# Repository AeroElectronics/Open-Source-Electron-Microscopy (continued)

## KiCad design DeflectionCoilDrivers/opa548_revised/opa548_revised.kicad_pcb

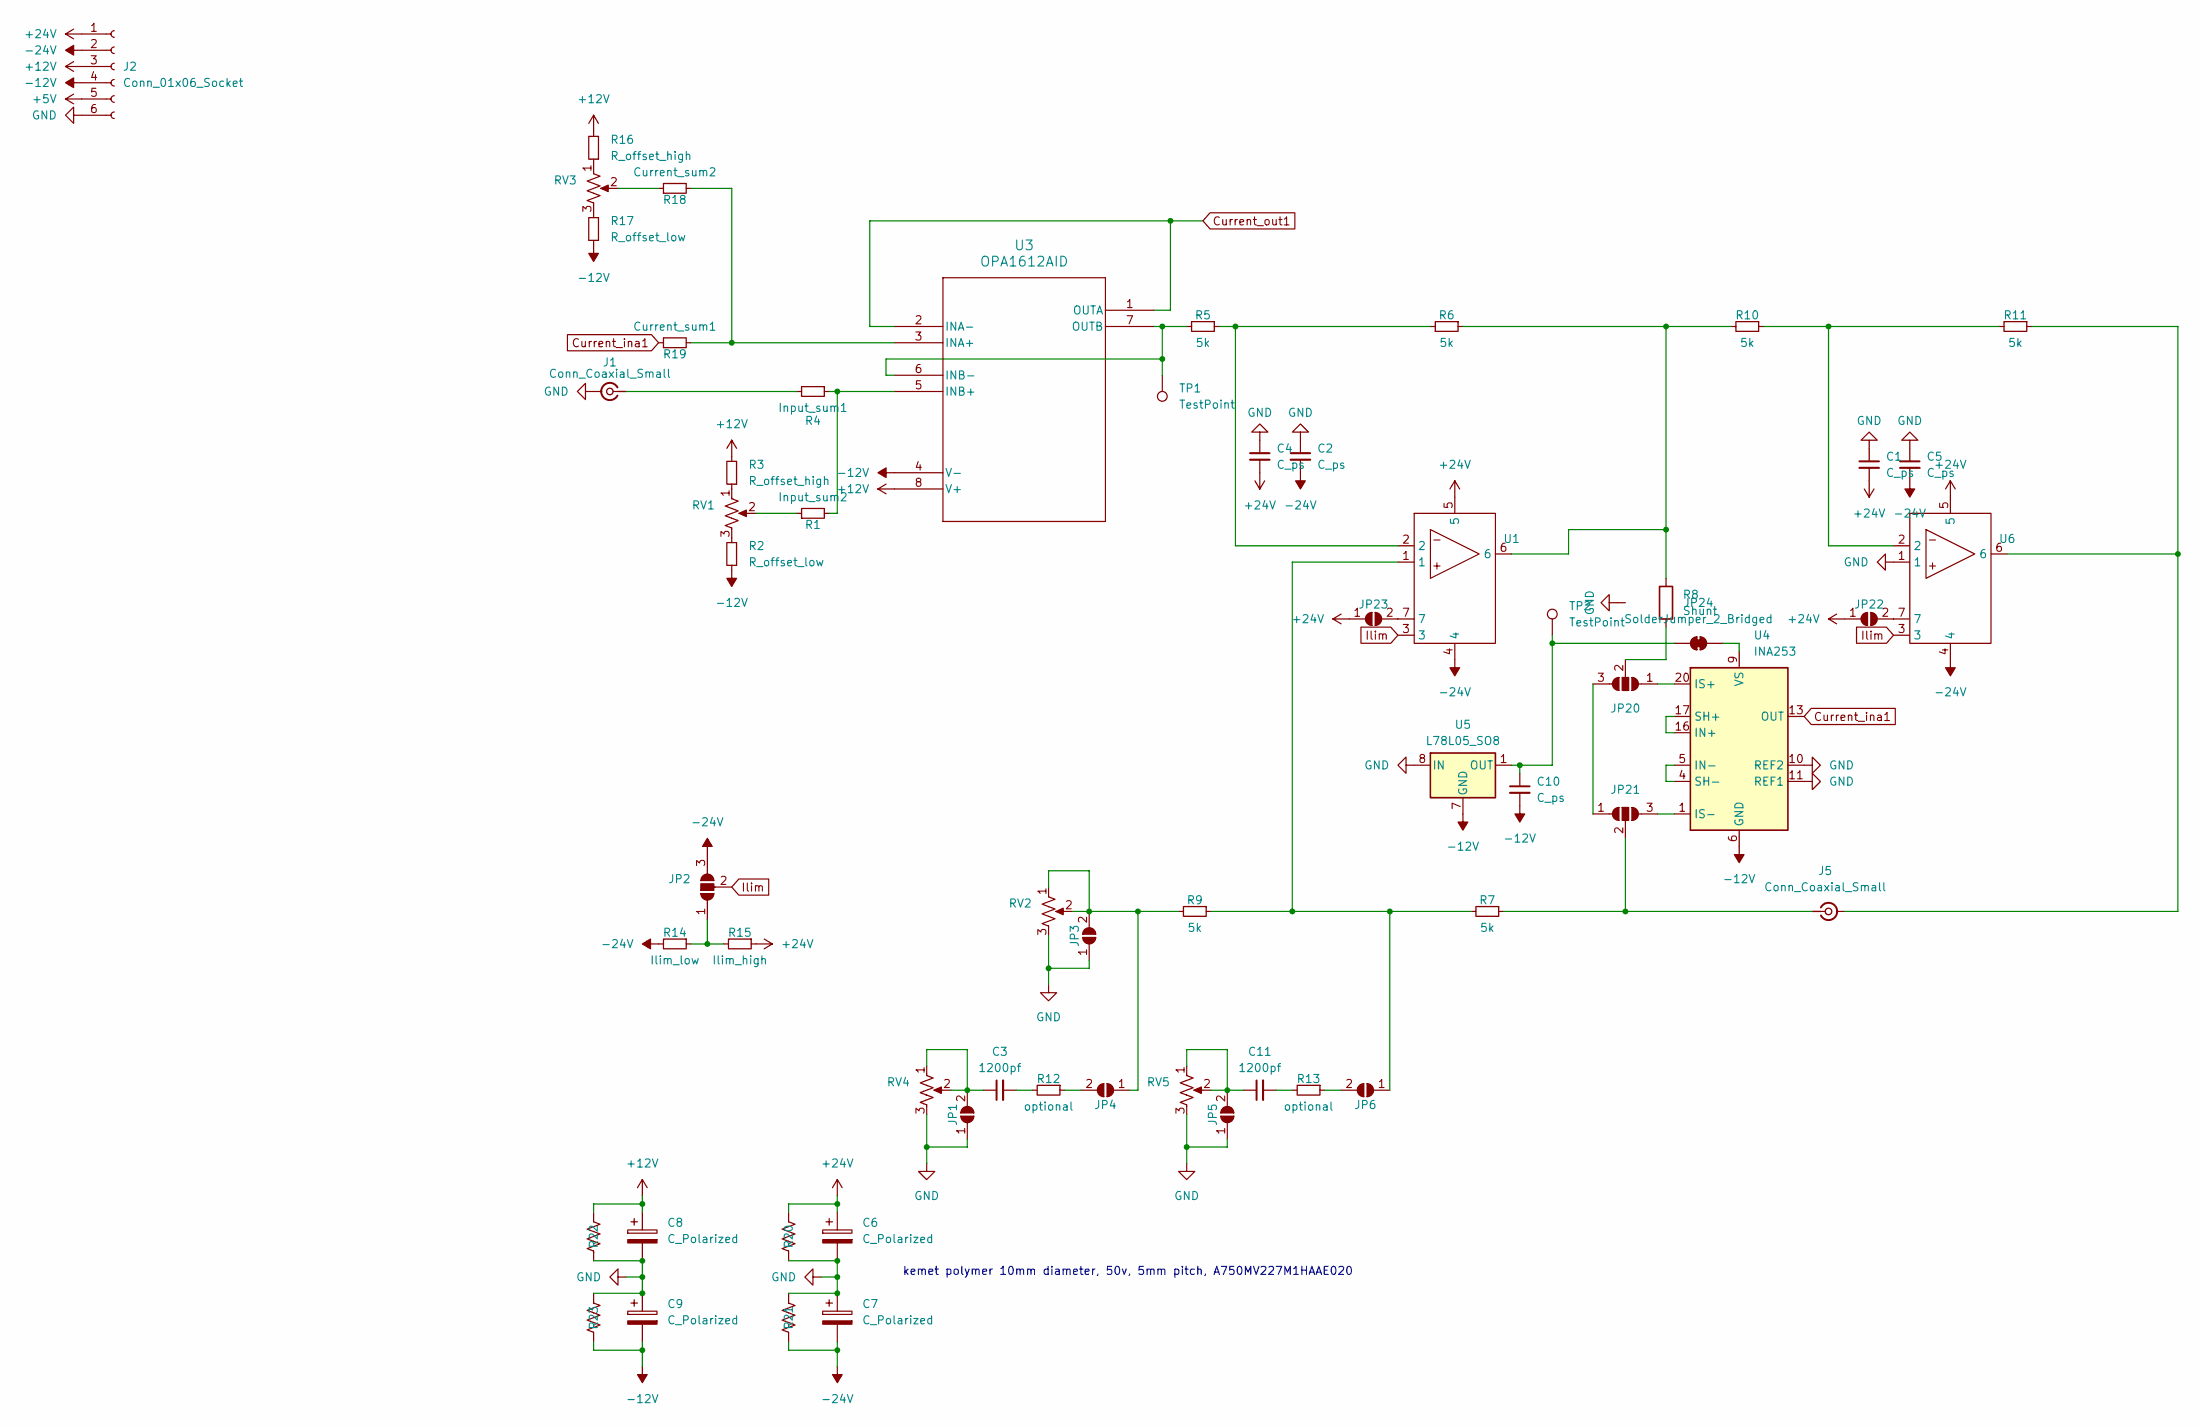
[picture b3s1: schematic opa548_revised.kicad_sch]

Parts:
C1, C2, C4, C5, C10: C_ps; C_0603_1608Metric_Pad1.08x0.95mm_HandSolder
C3, C11: 1200pf; C_0603_1608Metric_Pad1.08x0.95mm_HandSolder
C6, C7, C8, C9: C_Polarized; CP_Radial_D10.0mm_P5.00mm
J1, J5: Conn_Coaxial_Small; BNC_Amphenol_B6252HB-NPP3G-50_Horizontal
J2: Conn_01x06_Socket; PhoenixContact_MC_1,5_6-GF-3.81_1x06_P3.81mm_Horizontal_Thr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
JP1, JP3, JP4, JP5, JP6, JP22, JP23: SolderJumper_2_Open; SolderJumper-2_P1.3mm_Open_RoundedPad1.0x1.5mm
JP2, JP20, JP21: SolderJumper_3_Open; SolderJumper-3_P1.3mm_Open_RoundedPad1.0x1.5mm
JP24: SolderJumper_2_Bridged; SolderJumper-2_P1.3mm_Bridged_RoundedPad1.0x1.5mm
R1: Input_sum2; R_0603_1608Metric_Pad0.98x0.95mm_HandSolder
R2, R17: R_offset_low; R_0603_1608Metric_Pad0.98x0.95mm_HandSolder
R3, R16: R_offset_high; R_0603_1608Metric_Pad0.98x0.95mm_HandSolder
R4: Input_sum1; R_0603_1608Metric_Pad0.98x0.95mm_HandSolder
R5, R6, R7, R9, R10, R11: 5k; R_0603_1608Metric_Pad0.98x0.95mm_HandSolder
R8: Shunt; TO-263-2_TabPin1
R12, R13: optional; R_0603_1608Metric_Pad0.98x0.95mm_HandSolder
R14: Ilim_low; R_0603_1608Metric_Pad0.98x0.95mm_HandSolder
R15: Ilim_high; R_0603_1608Metric_Pad0.98x0.95mm_HandSolder
R18: Current_sum2; R_0603_1608Metric_Pad0.98x0.95mm_HandSolder
R19: Current_sum1; R_0603_1608Metric_Pad0.98x0.95mm_HandSolder
R20, R21, R22, R23: 100k; R_0603_1608Metric_Pad0.98x0.95mm_HandSolder
RV1, RV2, RV3, RV4, RV5: R_Potentiometer_US; Potentiometer_Bourns_3269P_Horizontal
TP1, TP2: TestPoint; PinSocket_1x01_P2.54mm_Vertical
U1, U6: opa548
U3: OPA1612AID; opa1612
U4: INA253; TSSOP-20_4.4x6.5mm_P0.65mm
U5: L78L05_SO8; SOIC-8_3.9x4.9mm_P1.27mm

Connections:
+5V: J2.5
+12V: C8.1, J2.3, R3.2, R16.2, R22.2, U3.8 (V+)
+24V: C1.2, C4.2, C6.1, J2.1, JP22.1 (A), JP23.1 (A), R15.1, R20.2, U1.5, U6.5
-12V: C9.2, C10.2, J2.4, R2.1, R17.1, R23.1, U3.4 (V-), U4.6 (GND), U4.15 (GND), U5.2 (GND), U5.3 (GND), U5.6 (GND), U5.7 (GND)
-24V: C2.2, C5.2, C7.2, J2.2, JP2.3 (B), R14.2, R21.1, U1.4, U6.4
Current_ina1: R19.1, U4.13 (OUT)
Current_out1: U3.1 (OUTA), U3.2 (INA-)
GND: C1.1, C2.1, C4.1, C5.1, C6.2, C7.1, C8.2, C9.1, J1.2 (Ext), J2.6, JP1.1 (A), JP3.1 (A), JP5.1 (A), R8.3, R20.1, R21.2, R22.1, R23.2, RV2.3, RV4.3, RV5.3, U4.10 (REF2), U4.11 (REF1), U5.8 (IN), U6.1
Ilim: JP2.2 (C), U1.3, U6.3
unnamed: C3.2, R12.2
unnamed: C11.2, R13.2
unnamed: J1.1 (In), R4.2
unnamed: J5.2 (Ext), R11.1, U6.6
unnamed: J5.1 (In), JP21.2 (C), R7.1
unnamed: C3.1, JP1.2 (B), RV4.1, RV4.2
unnamed: JP2.1 (A), R14.1, R15.2
unnamed: JP3.2 (B), JP4.1 (A), R9.2, RV2.1, RV2.2
unnamed: JP4.2 (B), R12.1
unnamed: C11.1, JP5.2 (B), RV5.1, RV5.2
unnamed: JP6.1 (A), R7.2, R9.1, U1.1
unnamed: JP6.2 (B), R13.1
unnamed: JP20.1 (A), U4.18 (IS+), U4.19 (IS+), U4.20 (IS+)
unnamed: JP20.3 (B), JP21.1 (A)
unnamed: JP20.2 (C), R8.2
unnamed: JP21.3 (B), U4.1 (IS-), U4.2 (IS-), U4.3 (IS-)
unnamed: JP22.2 (B), U6.7
unnamed: JP23.2 (B), U1.7
unnamed: C10.1, JP24.1 (A), TP2.1, U5.1 (OUT)
unnamed: JP24.2 (B), U4.9 (VS)
unnamed: R1.1, RV1.2
unnamed: R2.2, RV1.3
unnamed: R3.1, RV1.1
unnamed: R5.1, R6.2, U1.2
unnamed: R10.1, R11.2, U6.2
unnamed: R6.1, R8.1, R10.2, U1.6
unnamed: R16.1, RV3.1
unnamed: R17.2, RV3.3
unnamed: R18.1, RV3.2
unnamed: R18.2, R19.2, U3.3 (INA+)
unnamed: R1.2, R4.1, U3.5 (INB+)
unnamed: R5.2, TP1.1, U3.6 (INB-), U3.7 (OUTB)
unnamed: U4.16 (IN+), U4.17 (SH+)
unnamed: U4.4 (SH-), U4.5 (IN-)

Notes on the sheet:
kemet polymer 10mm diameter, 50v, 5mm pitch, A750MV227M1HAAE020

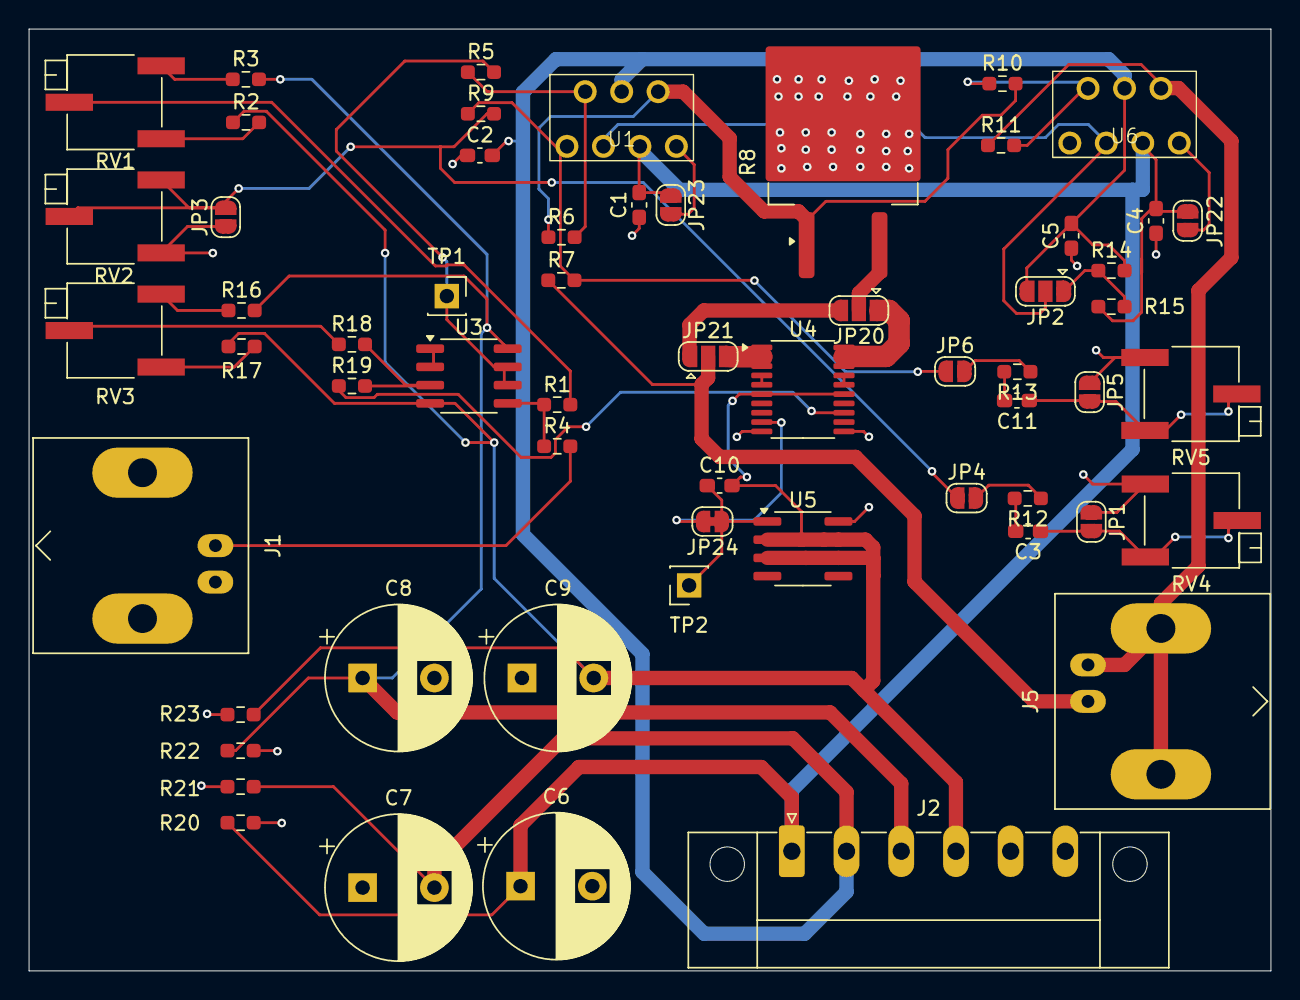
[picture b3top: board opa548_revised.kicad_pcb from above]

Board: 2 copper layers, 86.5 x 65.6 mm, 60 parts (0 on the bottom side), 42 nets.

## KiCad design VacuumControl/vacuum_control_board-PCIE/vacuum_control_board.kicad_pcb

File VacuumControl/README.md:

To open and close valves, read out voltages, or do whatver other control related tasks.

These boards are both STM32 microcontrollers with opto isolated output and analog IO hooked up to some headphone jacks. There are two versions, one with the microcontroller on a daugter board and one with the microcontroller layed out on the boards.

I havent tested this board yet, so you may want to hold off until I do. Also, I'm strongly considering switching to a raspberry pi or something else.

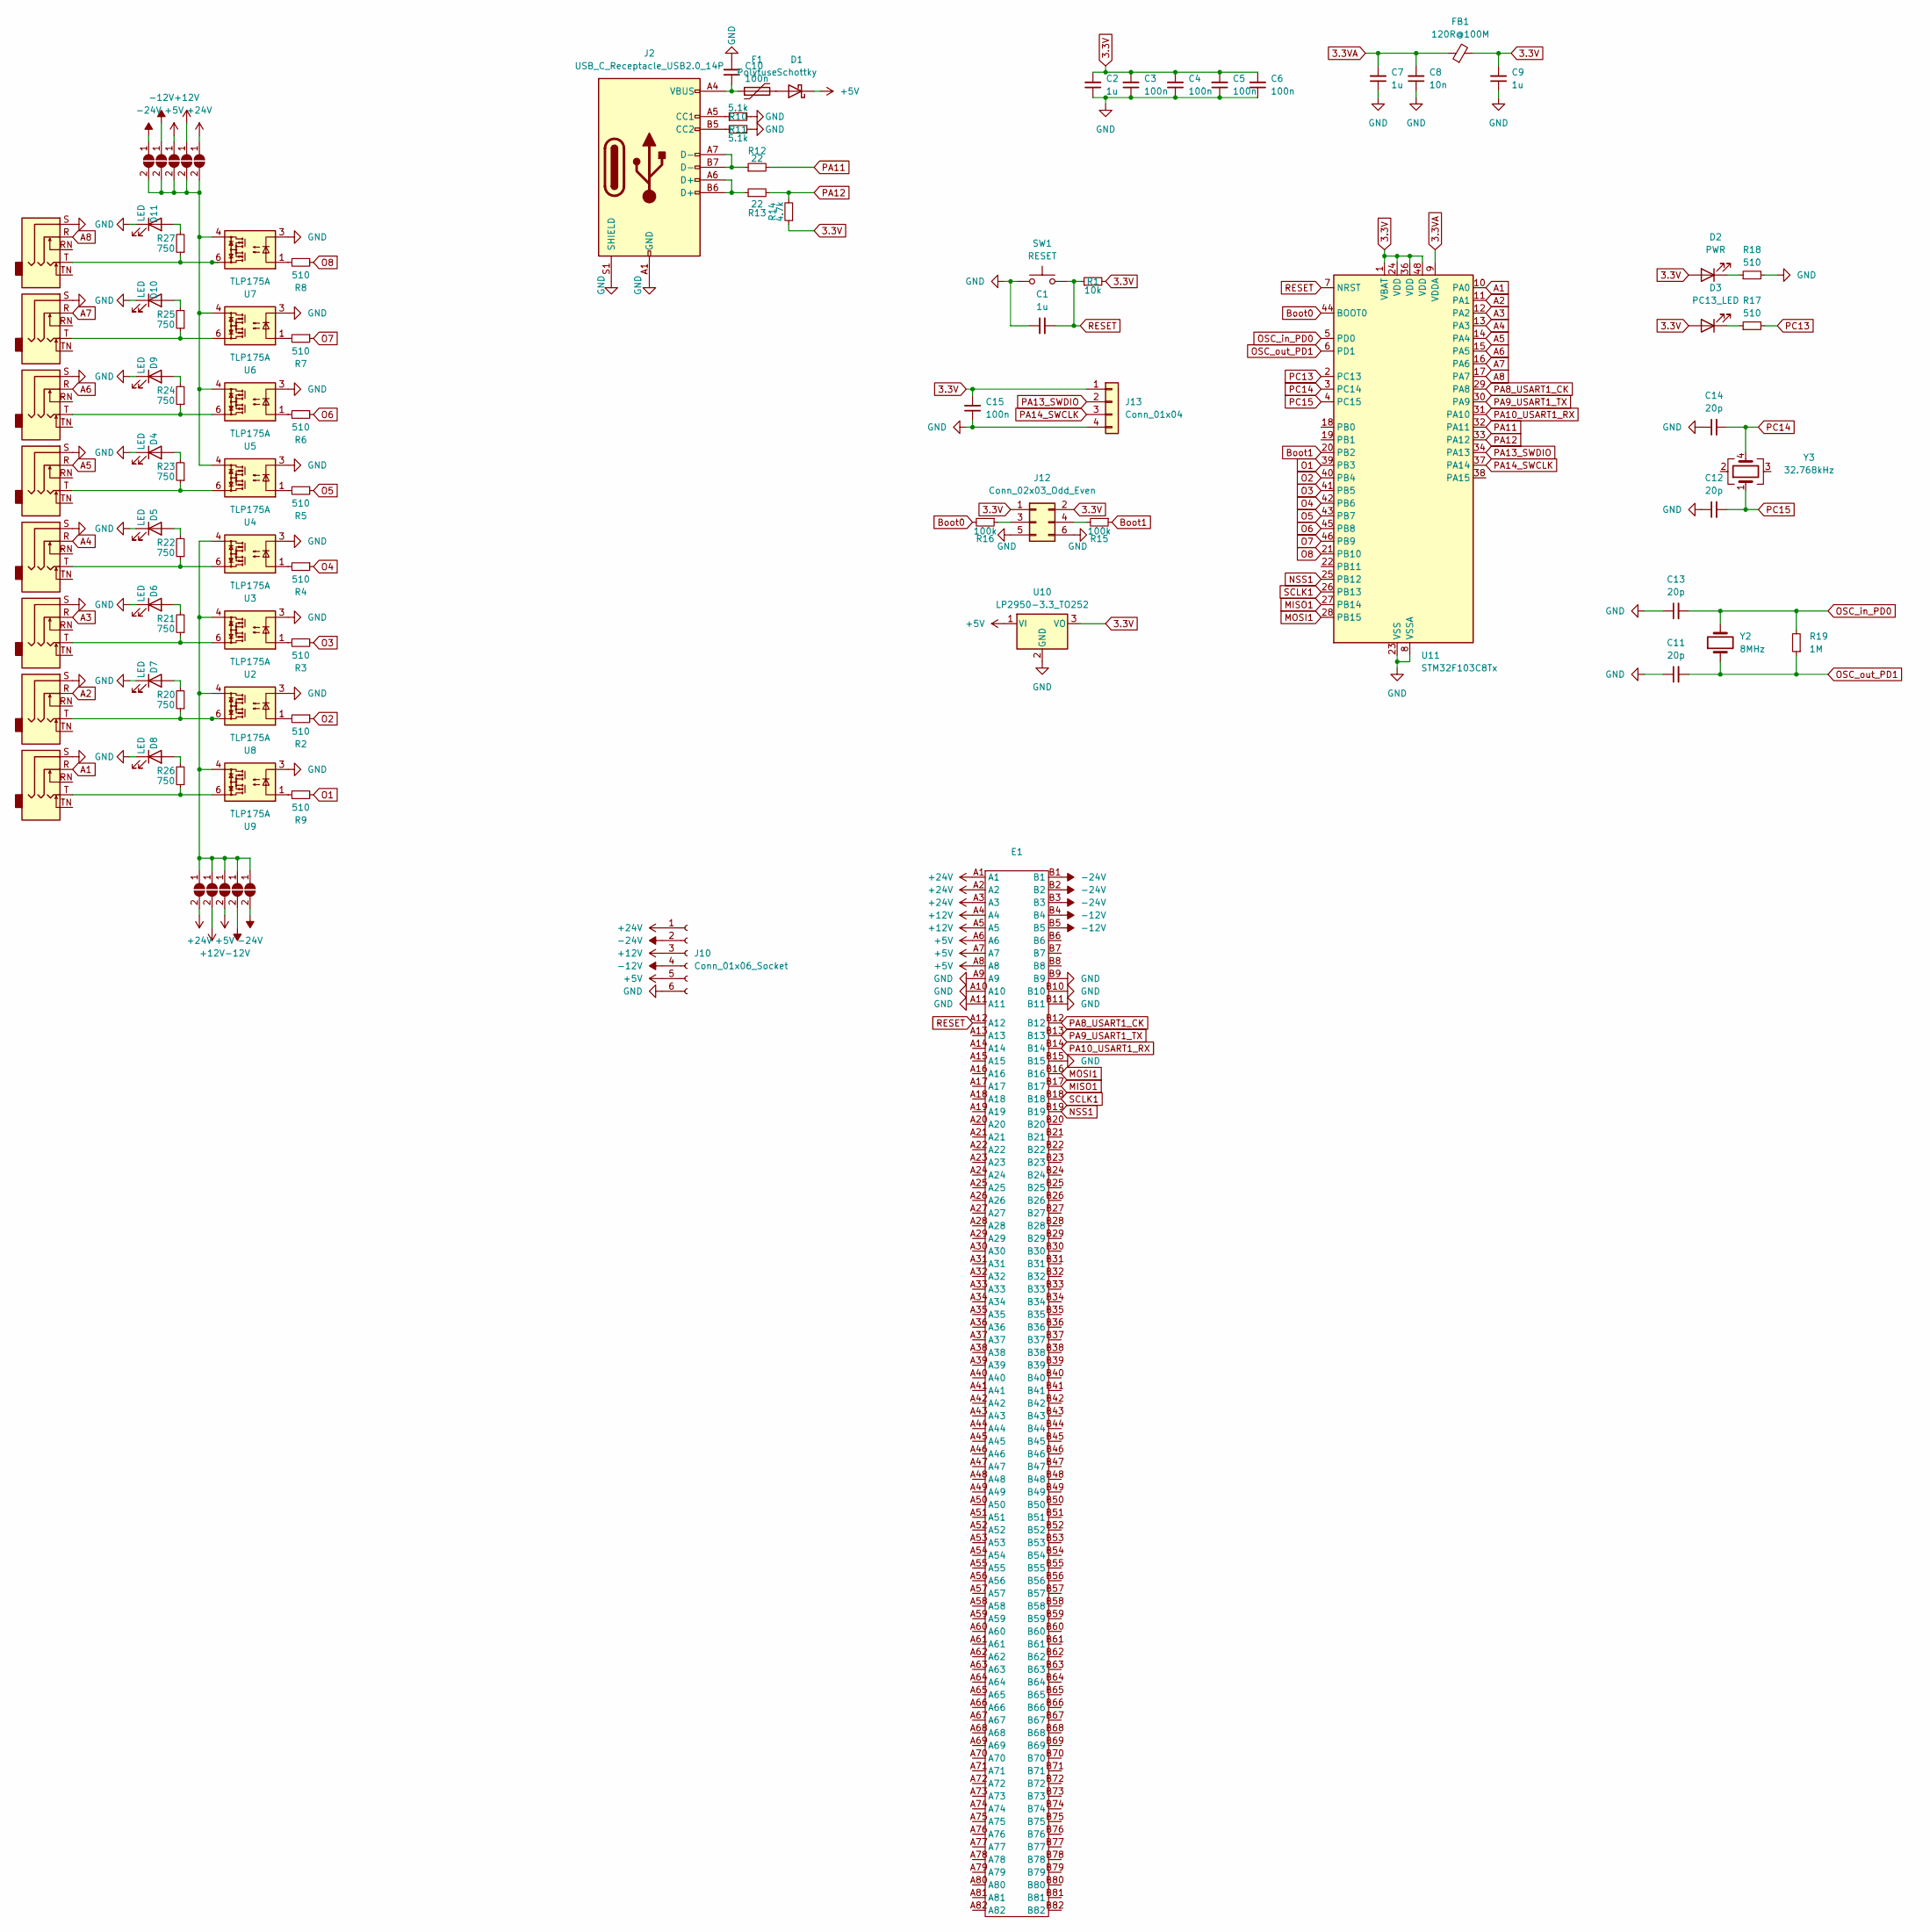
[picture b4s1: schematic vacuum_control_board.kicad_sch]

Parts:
C1, C2, C7, C9: 1u; C_0603_1608Metric_Pad1.08x0.95mm_HandSolder
C3, C4, C5, C6, C10, C15: 100n; C_0603_1608Metric_Pad1.08x0.95mm_HandSolder
C8: 10n; C_0603_1608Metric_Pad1.08x0.95mm_HandSolder
C11, C12, C13, C14: 20p; C_0603_1608Metric_Pad1.08x0.95mm_HandSolder
D1: Schottky; R_1210_3225Metric_Pad1.30x2.65mm_HandSolder
D2: PWR; LED_0603_1608Metric
D3: PC13_LED; LED_0603_1608Metric
D4, D5, D6, D7, D8, D9, D10, D11: LED; LED_0603_1608Metric_Pad1.05x0.95mm_HandSolder
E1: BUS_PCIexpress_x16
F1: Polyfuse; R_0603_1608Metric_Pad0.98x0.95mm_HandSolder
FB1: 120R@100M; C_0603_1608Metric_Pad1.08x0.95mm_HandSolder
J1, J3, J4, J5, J6, J7, J8, J9: AudioJack3_SwitchTR; Jack_3.5mm_CUI_SJ1-3535NG_Horizontal_CircularHoles
J2: USB_C_Receptacle_USB2.0_14P; USB_C_Receptacle_GCT_USB4105-xx-A_16P_TopMnt_Horizontal
J10: Conn_01x06_Socket; PhoenixContact_MC_1,5_6-GF-3.81_1x06_P3.81mm_Horizontal_Thr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
J12: Conn_02x03_Odd_Even; PinHeader_2x03_P2.54mm_Vertical
J13: Conn_01x04; PinSocket_1x04_P2.54mm_Vertical
JP1, JP2, JP3, JP4, JP5, JP6, JP7, JP8, JP9, JP10: SolderJumper_2_Open; SolderJumper-2_P1.3mm_Open_RoundedPad1.0x1.5mm
R1: 10k; R_0603_1608Metric_Pad0.98x0.95mm_HandSolder
R2, R3, R4, R5, R6, R7, R8, R9, R17, R18: 510; R_0603_1608Metric_Pad0.98x0.95mm_HandSolder
R10, R11: 5.1k; R_0603_1608Metric_Pad0.98x0.95mm_HandSolder
R12, R13: 22; R_0603_1608Metric_Pad0.98x0.95mm_HandSolder
R14: 4.7k; R_0603_1608Metric_Pad0.98x0.95mm_HandSolder
R15, R16: 100k; R_0603_1608Metric_Pad0.98x0.95mm_HandSolder
R19: 1M; R_0603_1608Metric_Pad0.98x0.95mm_HandSolder
R20, R21, R22, R23, R24, R25, R26, R27: 750; R_0603_1608Metric_Pad0.98x0.95mm_HandSolder
SW1: RESET; SW_Push_1P1T_NO_Vertical_Wuerth_434133025816
U2, U3, U4, U5, U6, U7, U8, U9: TLP175A; MFSOP6-4_4.4x3.6mm_P1.27mm
U10: LP2950-3.3_TO252; TO-252-2
U11: STM32F103C8Tx; LQFP-48_7x7mm_P0.5mm
Y2: 8MHz; Crystal_HC49-4H_Vertical
Y3: 32.768kHz; Crystal_SMD_SeikoEpson_MC306-4Pin_8.0x3.2mm_HandSoldering

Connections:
3.3V: C2.2, C3.2, C4.2, C5.2, C6.2, C9.2, C15.2, D2.2 (A), D3.2 (A), FB1.2, J12.1, J12.2, J13.1, R1.2, R14.1, U10.3 (VO), U11.1 (VBAT), U11.24 (VDD), U11.36 (VDD), U11.48 (VDD)
3.3VA: C7.2, C8.2, FB1.1, U11.9 (VDDA)
+5V: D1.1 (K), E1.A6, E1.A7, E1.A8, J10.5, JP2.1 (A), JP8.2 (B), U10.1 (VI)
+12V: E1.A4, E1.A5, J10.3, JP3.1 (A), JP9.2 (B)
+24V: E1.A1, E1.A2, E1.A3, J10.1, JP4.1 (A), JP10.2 (B)
-12V: E1.B4, E1.B5, J10.4, JP1.1 (A), JP7.2 (B)
-24V: E1.B1, E1.B2, E1.B3, J10.2, JP5.1 (A), JP6.2 (B)
A1: J3.R, U11.10 (PA0)
A2: J1.R, U11.11 (PA1)
A3: J4.R, U11.12 (PA2)
A4: J5.R, U11.13 (PA3)
A5: J6.R, U11.14 (PA4)
A6: J7.R, U11.15 (PA5)
A7: J8.R, U11.16 (PA6)
A8: J9.R, U11.17 (PA7)
Boot0: R16.2, U11.44 (BOOT0)
Boot1: R15.1, U11.20 (PB2)
GND: C1.1, C2.1, C3.1, C4.1, C5.1, C6.1, C7.1, C8.1, C9.1, C10.2, C11.1, C12.1, C13.1, C14.1, C15.1, D4.1 (K), D5.1 (K), D6.1 (K), D7.1 (K), D8.1 (K), D9.1 (K), D10.1 (K), D11.1 (K), E1.A9, E1.A10, E1.A11, E1.B9, E1.B10, E1.B11, E1.B15, J1.S, J2.A1 (GND), J2.A12 (GND), J2.B1 (GND), J2.B12 (GND), J2.S1 (SHIELD), J3.S, J4.S, J5.S, J6.S, J7.S, J8.S, J9.S, J10.6, J12.5, J12.6, J13.4, R10.2, R11.2, R18.2, SW1.1, U2.3, U3.3, U4.3, U5.3, U6.3, U7.3, U8.3, U9.3, U10.2 (GND), U11.8 (VSSA), U11.23 (VSS), U11.35 (VSS), U11.47 (VSS)
MISO1: E1.B17, U11.27 (PB14)
MOSI1: E1.B16, U11.28 (PB15)
NSS1: E1.B19, U11.25 (PB12)
unnamed: C10.1, F1.1, J2.A4 (VBUS), J2.A9 (VBUS), J2.B4 (VBUS), J2.B9 (VBUS)
unnamed: D1.2 (A), F1.2
unnamed: D2.1 (K), R18.1
unnamed: D3.1 (K), R17.1
unnamed: D4.2 (A), R23.2
unnamed: D5.2 (A), R22.2
unnamed: D6.2 (A), R21.2
unnamed: D7.2 (A), R20.2
unnamed: D8.2 (A), R26.2
unnamed: D9.2 (A), R24.2
unnamed: D10.2 (A), R25.2
unnamed: D11.2 (A), R27.2
unnamed: J1.T, R20.1, U8.6
unnamed: J2.A5 (CC1), R10.1
unnamed: J2.B5 (CC2), R11.1
unnamed: J2.A6 (D+), J2.B6 (D+), R13.1
unnamed: J2.A7 (D-), J2.B7 (D-), R12.1
unnamed: J3.T, R26.1, U9.6
unnamed: J4.T, R21.1, U2.6
unnamed: J5.T, R22.1, U3.6
unnamed: J6.T, R23.1, U4.6
unnamed: J7.T, R24.1, U5.6
unnamed: J8.T, R25.1, U6.6
unnamed: J9.T, R27.1, U7.6
unnamed: J12.3, R16.1
unnamed: J12.4, R15.2
unnamed: JP1.2 (B), JP2.2 (B), JP3.2 (B), JP4.2 (B), JP5.2 (B), U4.4, U5.4, U6.4, U7.4
unnamed: JP6.1 (A), JP7.1 (A), JP8.1 (A), JP9.1 (A), JP10.1 (A), U2.4, U3.4, U8.4, U9.4
unnamed: R2.2, U8.1
unnamed: R3.2, U2.1
unnamed: R4.2, U3.1
unnamed: R5.2, U4.1
unnamed: R6.2, U5.1
unnamed: R7.2, U6.1
unnamed: R8.2, U7.1
unnamed: R9.2, U9.1
O1: R9.1, U11.39 (PB3)
O2: R2.1, U11.40 (PB4)
O3: R3.1, U11.41 (PB5)
O4: R4.1, U11.42 (PB6)
O5: R5.1, U11.43 (PB7)
O6: R6.1, U11.45 (PB8)
O7: R7.1, U11.46 (PB9)
O8: R8.1, U11.21 (PB10)
OSC_in_PD0: C13.2, R19.2, U11.5 (PD0), Y2.2
OSC_out_PD1: C11.2, R19.1, U11.6 (PD1), Y2.1
PA8_USART1_CK: E1.B12, U11.29 (PA8)
PA9_USART1_TX: E1.B13, U11.30 (PA9)
PA10_USART1_RX: E1.B14, U11.31 (PA10)
PA11: R12.2, U11.32 (PA11)
PA12: R13.2, R14.2, U11.33 (PA12)
PA13_SWDIO: J13.2, U11.34 (PA13)
PA14_SWCLK: J13.3, U11.37 (PA14)
PC13: R17.2, U11.2 (PC13)
PC14: C14.2, U11.3 (PC14), Y3.4
PC15: C12.2, U11.4 (PC15), Y3.1
RESET: C1.2, E1.A12, R1.1, SW1.2, U11.7 (NRST)
SCLK1: E1.B18, U11.26 (PB13)

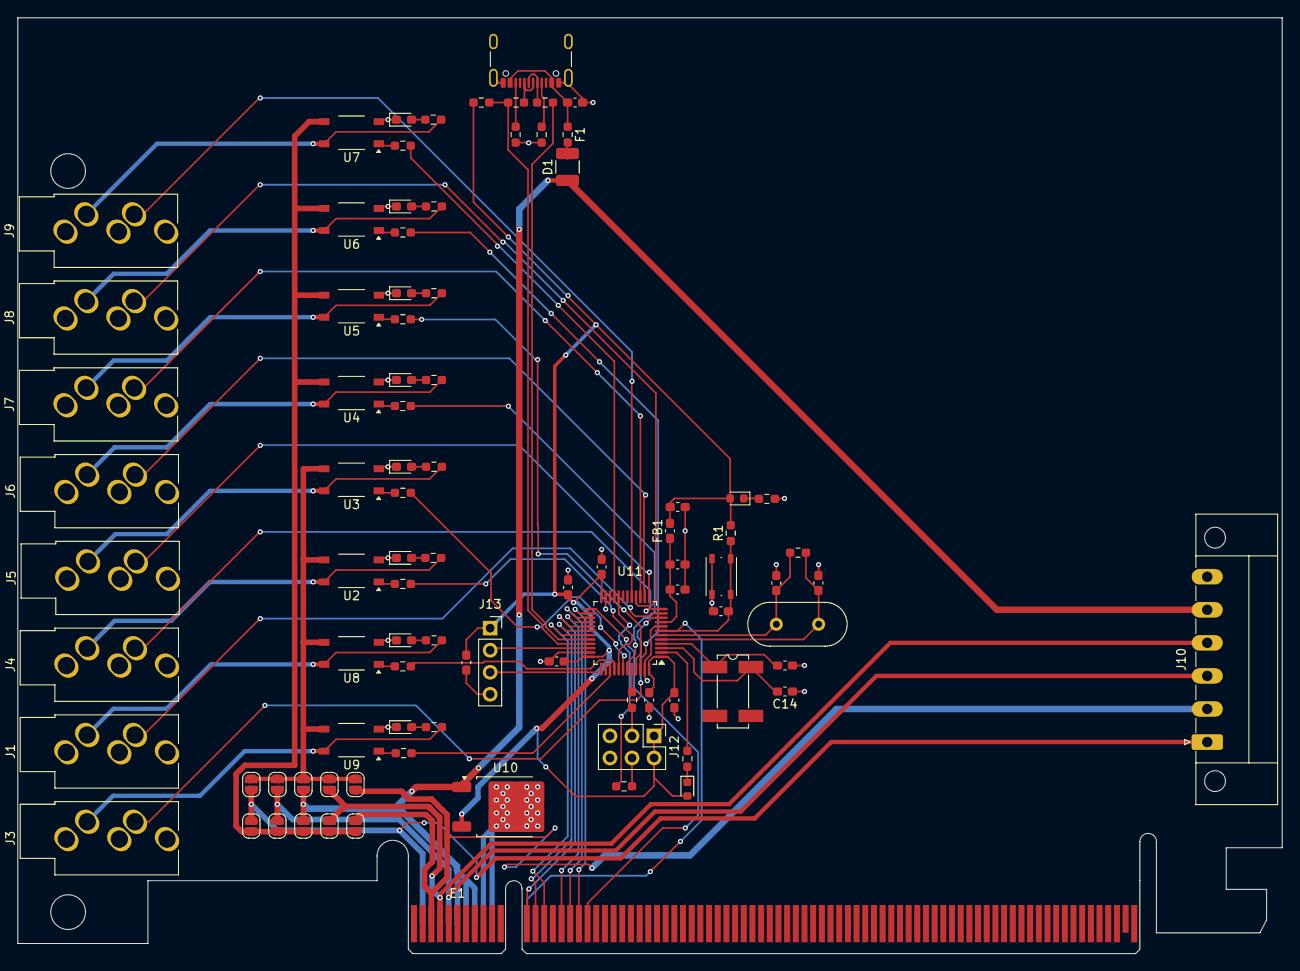
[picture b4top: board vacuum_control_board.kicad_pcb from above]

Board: 2 copper layers, 145.7 x 107.8 mm, 91 parts (0 on the bottom side), 79 nets.
